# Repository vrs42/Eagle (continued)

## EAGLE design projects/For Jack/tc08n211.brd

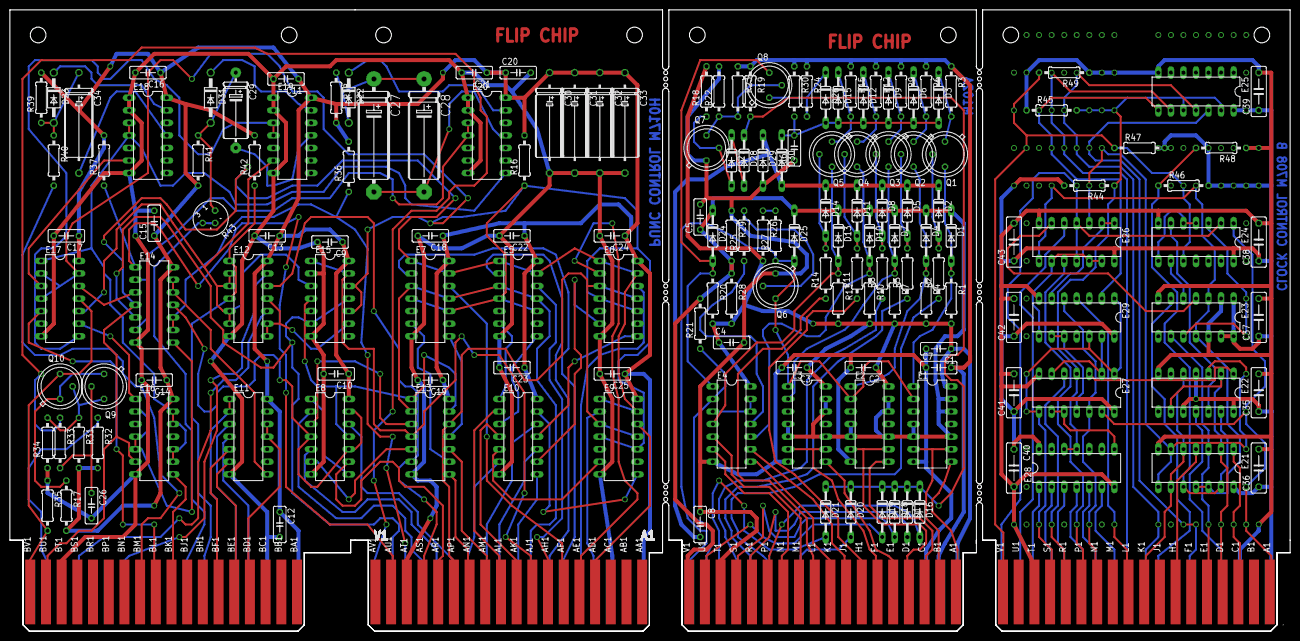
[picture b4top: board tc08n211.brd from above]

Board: 2 copper layers, 259.1 x 125.7 mm, 167 parts (0 on the bottom side), 179 nets.

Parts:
C1, C2, C3, C4, C5, C6, C7, C8: .01uF; C050-025X075
C9, C10, C11, C12, C13, C14, C15, C16, C17, C18, C19, C20, C21, C22, C23, C24, C25, C26: .01uf; C050-025X075
C27, C28: 150; E22-6
C29: 2.2uf; E15-5
C30, C31, C32, C33: 6.8uF; E12-8
C34: 180; E12-8
C35, C36, C37, C38, C39, C40, C41, C42, C43: .01uf; C075-032X103
D1, D2, D3, D4, D5, D6, D7, D8, D9, D10, D11, D12, D13, D14, D15, D16, D17, D18, D19, D20, D21, D24, D25, D26: 1N4154; DO35-10
D22, D23, D31: 1N4154; DO41-10
D27, D28, D29, D30: 1N914; DO35-10
E1, E2, E3: 74H40N; DIL14
E4, E8, E14, E24, E25, E26, E27: 7400N; DIL14
E5, E6, E7, E9, E15, E17, E22, E23: 7474N; DIL14
E10, E13: 7404N; DIL14
E11, E28: 7430N; DIL14
E12, E21: 7401N; DIL14
E16: 7440; DIL14
E18, E19, E20: 9601; DIL14
E29: 7420N; DIL14
E$1: DECPROTO211
Q1, Q2, Q3, Q4, Q5, Q6, Q8: PN3569; TO39
Q7: PN3640; TO39
Q9, Q10: DEC6534D; TO5
R1, R4, R7, R10, R13, R20, R45, R48, R49: 1.5K; 0207/10
R2, R5, R8, R11, R14: 470; 0207/10
R3, R6, R9, R12, R15: 1.8K; 0207/10
R16, R22, R36, R37, R42: 1K; 0207/10
R17: 56; 0207/10
R18: 47K; 0207/10
R19, R41: 15K; 0207/10
R21: 8.2K; 0207/10
R23: 3.3K; 0207/10
R24, R30: 2.7K; 0207/10
R25, R26, R27, R29, R44, R46, R47: 750; 0207/10
R28: 330; 0207/10
R31: 5.6K; 0207/10
R32: 100; 0207/10
R33, R34: 3K; 0207/10
R35: 150; 0207/10
R38, R39: 51K; 0207/10
R40: 7.5K; 0207/10
R43: 50K; RJ6
U$1, U$8: EDGE-CON2
U$2: EDGE-CON4
U$3: FLIPCHIP

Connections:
4.5MS: R43.E, R43.S, U$2.BJ2
4_SEC: R40.2, U$2.BM1
!CLEAR: E13.4, E15.1, E15.13, U$2.AJ1
!CLOCKB: E8.11, E13.1, E13.13, E15.4
!CLR_FLAG: E21.10, E21.13, E22.13, R46.1, R48.2
!FEED: E5.1, E5.13, E6.1, E6.13, E7.1, E7.13, E9.1, E9.13, E14.4, E16.6, U$2.BU1
!FEED_SW: E14.9, E14.10, R36.1, U$2.AT2
!INITIALIZE: E8.2, U$2.AS2
!IOP1: E25.9, U$1.L2
!IOP2: E27.5, U$1.R1
!IOP4: E25.12, U$1.F2
!IO_IN_INT: E12.10, U$2.BS2
!IO_IN_SKIP: E12.13, U$2.BN2
!IO_IRQ: E21.1, U$1.C1
!IO_SKIP: E21.4, U$1.H1
!MB3: E28.1, U$1.T2
!MB4: E28.2, U$1.S2
!MB6: E28.4, U$1.P2
!MB9: E27.12, E29.5, U$1.N1
!PUN_ACTIVE: E14.5, E15.6, E15.11, U$2.AU2
!SCR_ACTIVE: E16.8, U$2.BK1
+3V1: E25.10, E25.13, E27.4, E28.11, E28.12, R44.1, R45.2
+3V3: C5.1, D1.C, D4.C, D7.C, D10.C, D13.C, D24.C, D25.C, E1.4, E1.5, E1.10, E1.12, E1.13, E2.4, E2.5, E2.10, E2.12, E2.13, E3.4, E3.5, E3.10, E3.12, E3.13, R21.2, R28.1, R29.2, U$8.V1
-0.7V: C8.2, D2.C, D5.C, D8.C, D11.C, D14.C, D29.C, D30.A
-1.5V: C6.2, D3.A, D6.A, D9.A, D12.A, D15.A, D26.A, D30.C, R30.2
-15V: C7.2, R3.1, R6.1, R9.1, R12.1, R15.1, R19.1, R23.1, R24.1, R30.1, U$8.B2
A1: E1.8, U$8.A1
AC4: E5.12, U$2.AH1
AC5: E5.2, U$2.AH2
AC6: E7.12, U$2.AF1
AC7: E7.2, U$2.AF2
AC8: E6.2, U$2.AE1
AC9: E6.12, U$2.AE2
AC10: E9.12, U$2.AD1
AC11: E9.2, U$2.AD2
B1: E1.6, E1.9, U$8.B1
C1: E2.8, U$8.C1
CLOCK: E22.11, U$1.D2
CLOCKA: E5.3, E5.11, E7.3, E7.11, E13.2, U$2.AJ2
CLOCKB: E6.3, E6.11, E9.3, E9.11, E13.12, U$2.AP1
CLOCK_ENABLE: E23.6, U$1.J2
CLOCK_IOT: E27.1, E27.8, E29.1, E29.12, U$1.S1
D1: E2.6, E2.9, U$8.D1
DEL_PUN1: E14.1, R37.1, U$2.AU1
DEL_PUN2: E17.5, U$2.BL1
E1: E3.8, U$8.E1
F1: E3.6, E3.9, U$8.F1
FLAG: E21.2, E22.2, E22.9, U$1.D1
FLAG_BUFFER: E21.5, E21.9, E22.5, U$1.K1
GND: C1.2, C2.2, C3.2, C4.2, C5.2, C6.1, C7.1, C8.1, D29.A, E1.7, E2.7, E3.7, E4.7, Q6.1, Q7.1, R22.2, R29.1, U$8.C2, U$8.T1
GND1: C9.2, C10.2, C11.2, C12.2, C13.2, C14.2, C15.2, C16.2, C17.2, C18.2, C19.2, C20.2, C21.2, C22.2, C23.2, C24.2, C25.2, C26.2, C30.-, C31.-, C32.-, C33.-, E5.7, E6.7, E7.7, E8.7, E9.7, E10.7, E11.7, E12.7, E13.7, E14.7, E15.2, E15.7, E16.7, E17.7, E18.1, E18.2, E18.7, E19.1, E19.2, E19.7, E20.1, E20.2, E20.7, R34.1, R35.1, U$2.AC2, U$2.AT1, U$2.BC2, U$2.BT1
GND2: C35.2, C36.2, C37.2, C38.2, C39.2, C40.2, C41.2, C42.2, C43.2, E21.7, E22.7, E23.2, E23.7, E23.12, E24.7, E25.7, E26.7, E27.7, E28.7, E29.7, R45.1, R48.1, R49.1, U$1.C2, U$1.T1
H1: R11.1, U$8.H1
INITIALIZE: E26.10, U$1.P1
IOP1: E8.5, U$2.AR2
IOP2: E8.9, U$2.AR1
IOP3: E25.8, E29.2
IOP4: E8.12, U$2.AP2
IOP5: E25.11, U$1.K2
IOP6: E27.2, E27.6, E29.13
IOP_02: E12.12, E13.6, U$2.AS1
IRQ_ENB: E21.3, E23.9, U$1.E1
J1: E4.9, U$8.J1
K1: E4.8, U$8.K1
L1: R14.1, U$8.L1
LOAD_COUNTER: E24.2, E26.4, E26.11, U$1.V2
M1: E4.5, U$8.M1
M2: D20.A, U$8.M2
MB3(0): E11.1, E11.2, U$2.BF2
MB4(0): E11.11, E11.12, U$2.BD1
MB5: E28.3, U$1.R2
MB5(0): E11.4, U$2.BD2
MB6(0): E11.6, U$2.BE1
MB7: E28.5, U$1.N2
MB7(1): E11.3, U$2.BE2
MB8: E28.6, U$1.M2
MB8(0): E11.5, U$2.BF1
MB9: E26.5, U$1.U2
MB10: E29.4, U$1.L1
MB11: E24.1, E27.13, U$1.A1
MOTOR: E16.9, E16.10, E16.12, E16.13, E17.1, E18.3, E18.4, E20.8
N1: E4.6, U$8.N1
unnamed: D27.A, Q7.2, R18.1
unnamed: E4.11, R25.1
unnamed: Q6.2, R25.2
unnamed: D27.C, D28.A
unnamed: R26.1, R27.2
unnamed: Q7.3, Q8.2, R22.1, R23.2
unnamed: D26.C, Q8.1, R24.2
unnamed: D24.A, E4.1, Q8.3, R20.1
unnamed: E4.3, E4.12, E4.13
unnamed: D10.A, E4.10, Q4.3, R10.1
unnamed: D11.A, Q4.2, R11.2
unnamed: D16.C, D17.C, D18.C, D19.C, D20.C, D21.C, D28.C, R19.2
unnamed: D1.A, E1.1, Q1.3, R1.1
unnamed: D12.C, Q4.1, R12.2
unnamed: D13.A, E4.4, Q5.3, R13.1
unnamed: D14.A, Q5.2, R14.2
unnamed: D2.A, Q1.2, R2.2
unnamed: D15.C, Q5.1, R15.2
unnamed: D3.C, Q1.1, R3.2
unnamed: D4.A, E2.1, Q2.3, R4.1
unnamed: D5.A, Q2.2, R5.2
unnamed: D6.C, Q2.1, R6.2
unnamed: D7.A, E3.2, Q3.3, R7.1
unnamed: D8.A, Q3.2, R8.2
unnamed: D9.C, Q3.1, R9.2
unnamed: E11.8, E14.12, E14.13
unnamed: E8.1, E8.8
unnamed: E8.4, E8.10, E8.13, E14.11
unnamed: E5.8, E10.3
unnamed: E5.6, E10.1
unnamed: E6.6, E10.9
unnamed: E6.8, E10.11
unnamed: E9.8, E10.13
unnamed: E9.6, E10.5
unnamed: E7.8, E13.11
unnamed: E7.6, E13.9
unnamed: E8.3, E13.3
unnamed: E8.6, E13.5
unnamed: Q9.3, Q10.2, R31.1, R34.2
unnamed: Q9.1, Q10.1, R17.1
unnamed: C26.1, Q9.2, R33.2
unnamed: E14.8, E16.2, E16.4, E16.5
unnamed: C34.-, E18.11
unnamed: E14.2, E14.6, E20.3, E20.4
unnamed: E12.2, E12.3, E12.5, E12.6, E15.3, E17.10, E19.6
unnamed: E17.8, E19.3, E19.4
unnamed: E5.4, E5.10, E6.4, E6.10, E7.4, E7.10, E9.4, E9.10, E15.10, E15.12, E17.2, E17.4, E17.13, R16.1
unnamed: C29.-, E19.11
unnamed: E16.1, E17.9
unnamed: E14.3, E17.12
unnamed: C27.-, C28.-, E20.11
unnamed: D22.C, E20.13
unnamed: C27.+, C28.+, D22.A, R38.1
unnamed: D23.C, E18.13
unnamed: C34.+, D23.A, R39.1, R40.1
unnamed: E17.3, E18.6
unnamed: D31.C, E19.13
unnamed: C29.+, D31.A, R41.1, R43.A
unnamed: E27.9, E27.10, E28.8
unnamed: E22.1, E27.3
unnamed: E26.1, E26.2, E29.6
unnamed: E27.11, E29.9, E29.10
unnamed: E26.9, E26.12, E26.13, E29.8
unnamed: E23.4, E26.6
unnamed: E23.10, E24.3
unnamed: E21.6, E21.8, E22.3, E26.3
unnamed: E23.5, E24.9
unnamed: E24.4, E24.5, E24.8
unnamed: E22.12, E24.6
unnamed: E21.11, E21.12, E23.3, E23.11, E26.8
OVERFLOW: E24.10, R47.1, R49.2, U$1.V1
P1: D16.A, U$8.P1
P2: R2.1, U$8.P2
PB0: E10.4, U$2.AK1
PB1: E10.2, U$2.AL1
PB2: E13.10, U$2.AM1
PB3: E13.8, U$2.AN1
PB4: E10.8, U$2.AK2
PB5: E10.10, U$2.AL2
PB6: E10.12, U$2.AM2
PB7: E10.6, U$2.AN2
PUN_DONE: E12.1, E12.4, R42.1, U$2.BH2
PUN_FLAG: E12.8, E12.9, E12.11, E15.9
R1: D17.A, U$8.R1
R2: R5.1, U$8.R2
S1: D18.A, U$8.S1
S2: R8.1, U$8.S2
SYNC_BIAS: R32.1, U$2.BU2
SYNC_PUN: R33.1, U$2.AV2
SYNC_PUN0: E17.11, Q10.3, R35.2, U$2.BV1
T2: D21.A, U$8.T2
U1: D19.A, U$8.U1
U2: E4.2, R21.1, U$8.U2
V2: D25.A, E1.2, E2.2, E3.1, Q6.3, R27.1, U$8.V2
VCC: C1.1, C2.1, C3.1, C4.1, E1.14, E2.14, E3.14, E4.14, R1.2, R4.2, R7.2, R10.2, R13.2, R18.2, R20.2, R26.2, R28.2, U$8.A2
VCC1: C9.1, C10.1, C11.1, C12.1, C13.1, C14.1, C15.1, C16.1, C17.1, C18.1, C19.1, C20.1, C21.1, C22.1, C23.1, C24.1, C25.1, C30.+, C31.+, C32.+, C33.+, E5.14, E6.14, E7.14, E8.14, E9.14, E10.14, E11.14, E12.14, E13.14, E14.14, E15.14, E16.14, E17.14, E18.14, E19.14, E20.14, R16.2, R17.2, R31.2, R32.2, R36.2, R37.2, R38.2, R39.2, R41.2, R42.2, U$2.AA2, U$2.BA2
VCC2: C35.1, C36.1, C37.1, C38.1, C39.1, C40.1, C41.1, C42.1, C43.1, E21.14, E22.4, E22.10, E22.14, E23.1, E23.13, E23.14, E24.14, E25.14, E26.14, E27.14, E28.14, E29.14, R44.2, R46.2, R47.2, U$1.A2

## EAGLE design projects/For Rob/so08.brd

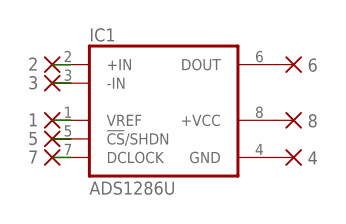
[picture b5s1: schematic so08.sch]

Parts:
1, 2, 3, 4, 5, 6, 7, 8: PAD-0360; 0360
IC1: ADS1286U; SO08

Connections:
unnamed: 8.P$1, IC1.8 (+VCC)
unnamed: 7.P$1, IC1.7 (DCLOCK)
unnamed: 5.P$1, IC1.5 (!CS!/SHDN)
unnamed: 1.P$1, IC1.1 (VREF)
unnamed: 2.P$1, IC1.2 (+IN)
unnamed: 3.P$1, IC1.3 (-IN)
unnamed: 4.P$1, IC1.4 (GND)
unnamed: 6.P$1, IC1.6 (DOUT)

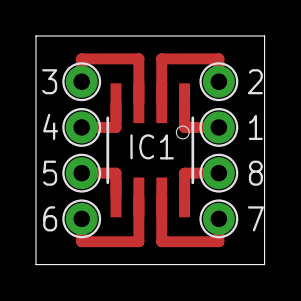
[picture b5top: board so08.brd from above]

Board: 2 copper layers, 12.7 x 12.7 mm, 9 parts (0 on the bottom side), 8 nets.
